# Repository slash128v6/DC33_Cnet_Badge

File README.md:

# DC33 CompuNet Badge - The Meshtastic Express

Introducing **The Meshtastic Express** — the open-source, networkless pager built for hackers, tinkerers, and technophiles. Powered by the Meshtastic protocol and fully customizable from the firmware up, this device lets you send messages over a decentralized mesh network — no cell towers, no Wi-Fi, no problem. Flash your own firmware, tweak the hardware with this highly customizable device and relive the 1990’s glory of belt-clip attached electronics.

Meshtastic devices use **LoRa (Long Range)** radio technology to send small data packets over several kilometers. Each device acts as a node in the mesh, forwarding messages to others until they reach their destination. Learn more at: 

[https://github.com/slash128v6/DC33_Cnet_Badge](https://github.com/slash128v6/DC33_Cnet_Badge)

[https://meshtastic.org](https://github.com/slash128v6/DC33_Cnet_Badge)

> [!TIP]
> **WARNING – DO NOT POWER THE HELTEC V3 LoRa UNIT WITHOUT THE ANTENNA ATTACHED! DAMAGE MAY RESULT**

# Section 1: Hardware Assembly

1.	Verify inventory:

| Qty	| Description |
|------|-------------|
|1	|PCB |
|1	|Heltec V3 LoRa Module Kit (includes antenna and 2x 18 pin headers)|
|1	|LiPo Battery|
|1	|GPS Module|
|1	|GPS Antenna|
|1	|Piezo Buzzer|
|1	|Vibration Motor|
|1	|6 Pin SAO Header|
|1	|12 Pin Header|
|2	|VHB Pads|
|1	|Case Bottom|
|1	|Case Top|
|1	|Case Clip|

2.	Solder the vibration motor. You can trim the wires but be very careful when stripping the ends, as the wire is very small gauge and easy to cut when stripping. Peel off the white tab and stick to the PCB. 

3.	Solder the 6 pin SAO header with the tab aligned with the white silkscreen outline. Try to keep it as square as possible so SAOs are not crooked when installed. 

4.	Solder the piezo buzzer noting the polarity. Remove the protective white sticker.

5.	Solder the Heltec V3 LoRo module to the PCB using the 2x 18 pin headers included in the kit. The short side of the pins should face up through the module and the long side should face down through the PCB. To save time soldering, only the pins marked with white dots need to be soldered. Be careful soldering the 2 pins under the display ribbon cable. The cable is heat resistant, but can melt with too much heat.

6.	Cut off 4 pins from the 12 pin header and solder the GPS module to the PCB. The short side of the pins should face up through the module and the long side should face down through the PCB.

7.	Attach the GPS antenna to the GPS module, pressing the connectors together until there is a slight click and they are parallel when viewed from the side. A fingernail or small flat bladed tool is helpful. Using one of the VHB pads affix the GPS antenna to the PCB, routing the wire underneath the lip. Make sure the GPS antenna is within the white square outline so the case will fit on later.

8.	Mount the PCB in the lower case. Route the LoRa antenna horizontally along the top edge of the PCB as shown. A piece of tape helps. Align the top half of the case onto the lower half posts and press together until the gap between the two halves is gone. 

Slide the clip into the opening on the back until it clicks into place. 

# Section 2: Flashing & Configuration

1.	Install the CP210x Universal Windows Driver from https://www.silabs.com/developer-tools/usb-to-uart-bridge-vcp-drivers?tab=downloads. 

2.	Connect the Heltec Lora V3 module to your PC with a USB-C cable. Open a browser to flasher.meshtastic.org. 

3.	Click “Select Target Device” and select the “Heltec V3” device. 

4.	Select the latest stable firmware from the dropdown menu. 

5.	Click “Flash”. 

6.	Click “Continue”.

7.	Toggle on the options “Full Erase and Install” and “Bundle Web UI” and click “Erase Flash and Install”. 

8.	A selection dialog will appear. Select the CP2102 device and click “Connect”. 

9.	Flashing will begin. Wait for it to complete. 

10. Go to client.meshtastic.org and click “New Connection”. Don’t leave the flasher page open in another tab as it can interfere with the client connection. 

11. Click on the “Serial” tab, then “New Device”. 

12. A selection dialog will appear. Select the CP2102 device and click “Connect”. 

13. Click the new device that appears. 

14. Click on Config in the left menu, then the LoRa tab, set the location to “US”, then click the save floppy icon in the upper right corner. After the setting is saved the Heltec module will reboot. If it does not then try refreshing the page and try again.

15. Reconnect and click on the Display tab, set the Carousel Display to “15”, then click the save floppy icon in the upper right corner. After the setting is saved the Heltec module will reboot. If it does not then try refreshing the page and try again.

16. Reconnect and click on the Position tab, set GPS Mode to Enables, the Receive Pin to “48” and the Transmit Pin to “47” then click the save floppy icon in the upper right corner. After the setting is saved the Heltec module will reboot. If it does not then try refreshing the page and try again.

17. Reconnect and click on Config and Module Config in the left menu, then the Ext Notif tab. Toggle on Enable External Notification then set Output Vibrate to “45” and Output Buzzer to “46” and enable all the toggle items EXCEPT “Use I2S Pin as Buzzer”, then click the save floppy icon in the upper right corner. After the setting is saved the Heltec module will reboot. If it does not then try refreshing the page and try again.

# Section 3: Operation

1.	There are 2 buttons on the left side of the display. Some common button commands:

	*	Brief single presses of the top button will cycle through the screens on the display. By default the screen will turn off after 15 seconds. You can use the top button to wake the display. You can also set a longer screen timeout in settings.
	
	*	A long press of the top button will put the device in shutdown mode.

	*	A triple short press of the top button will disable GPS. Repeat to re-enable GPS.

	*	A single press of the top button will wake it back up. A single press of the bottom button will reboot the device. 

2.	Download the Meshtastic app to your mobile device. It is supported on iOS and Android. Enable Bluetooth on your mobile device then open the Meshtastic app and go to the “Bluetooth” tab. You should see a list of available radios. Tap the radio with the ID that matches your device. You can view it on the info screen by cycling through with the top button.

3.	It will ask for a PIN that will be displayed on your radio’s display. Enter that PIN to connect

4.	The “Messages” tab is where you will send and receive messages. The “Primary Channel” reaches everyone on the mesh. 

5.	At this point you should have basic functionality. Feel free to explore the docs at [https://meshtastic.org/docs/introduction/](https://github.com/slash128v6/DC33_Cnet_Badge). Settings can be managed in the app as well, vs connecting to a PC and using the web interface at [https://client.meshtastic.org/](https://github.com/slash128v6/DC33_Cnet_Badge), though the web interface has more functionality. There is also a Python cli interface that allows bulk configuration changes and backup & restore. This is also covered on the Meshtastic website. A YAML config file with the basic settings applied in this doc is included in the “Software/configs” directory of the repo.

```
# start of Meshtastic configure yaml
config:
  device:
    buzzerGpio: 46
  display:
    autoScreenCarouselSecs: 15
    screenOnSecs: 31536000
  lora:
    region: US
  position:
    gpsMode: ENABLED
    rxGpio: 48
    txGpio: 47
module_config:
  externalNotification:
    active: true
    alertBell: true
    alertBellBuzzer: true
    alertBellVibra: true
    alertMessage: true
    alertMessageBuzzer: true
    alertMessageVibra: true
    enabled: true
    outputBuzzer: 46
    outputVibra: 45
    usePwm: true
```

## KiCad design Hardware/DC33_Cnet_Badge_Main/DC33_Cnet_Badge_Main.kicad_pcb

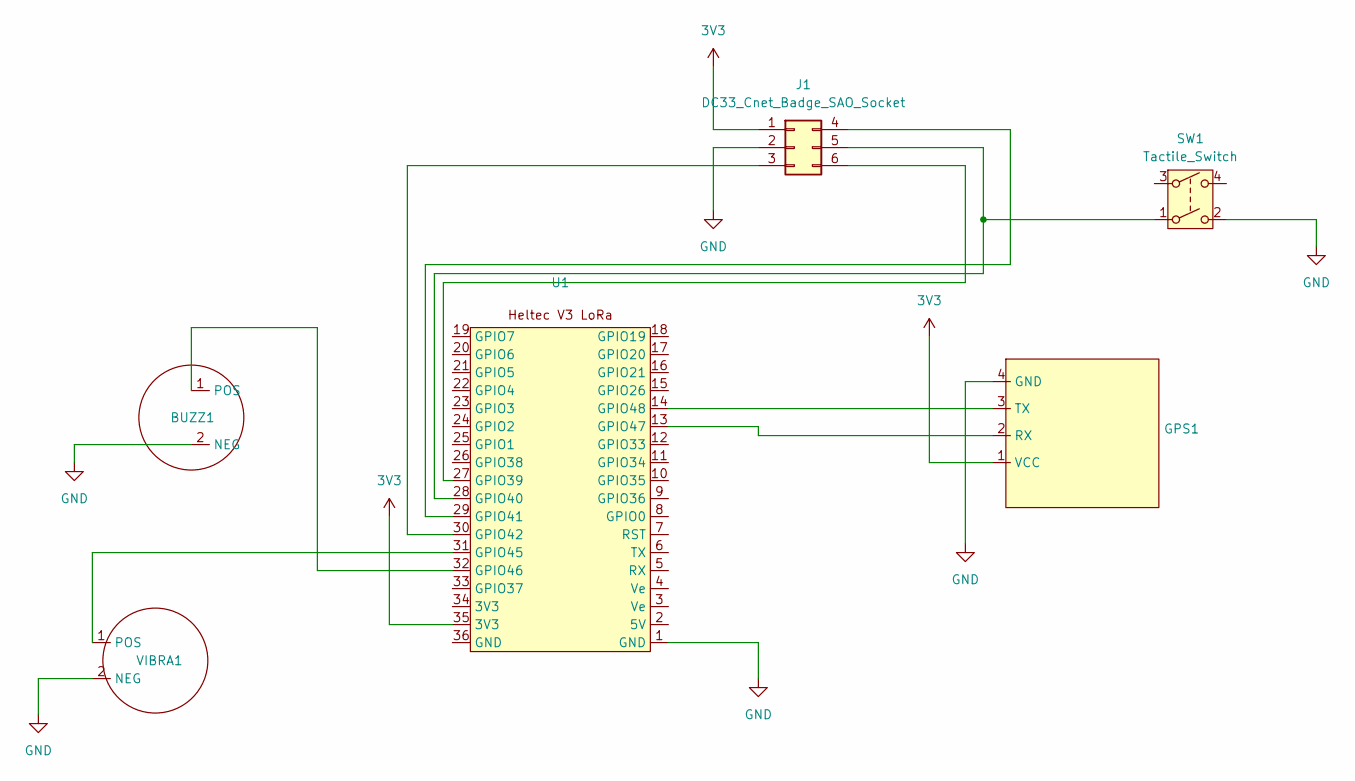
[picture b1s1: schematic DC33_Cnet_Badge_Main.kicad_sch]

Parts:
BUZZ1: DC33_Cnet_Badge_Buzzer
GPS1: DC33_Cnet_Badge_HiLetgo_GPS
J1: DC33_Cnet_Badge_SAO_Socket
SW1: Tactile_Switch; Tactile_Switch-13mm
U1: DC33_Cnet_Badge_Heltec_V3_LoRa
VIBRA1: DC33_Cnet_Badge_Vibra

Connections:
3V3: GPS1.1 (VCC), J1.1 (+3.3V), U1.35 (3V3)
GND: BUZZ1.2 (NEG), GPS1.4 (GND), J1.2 (GND), SW1.2, U1.1 (GND), VIBRA1.2 (NEG)
unnamed: BUZZ1.1 (POS), U1.32 (GPIO46)
unnamed: GPS1.2 (RX), U1.13 (GPIO47)
unnamed: GPS1.3 (TX), U1.14 (GPIO48)
unnamed: J1.5 (GPIO1), SW1.1, U1.28 (GPIO40)
unnamed: J1.6 (GPIO2), U1.27 (GPIO39)
unnamed: J1.4 (SCL), U1.29 (GPIO41)
unnamed: J1.3 (SDA), U1.30 (GPIO42)
unnamed: U1.31 (GPIO45), VIBRA1.1 (POS)

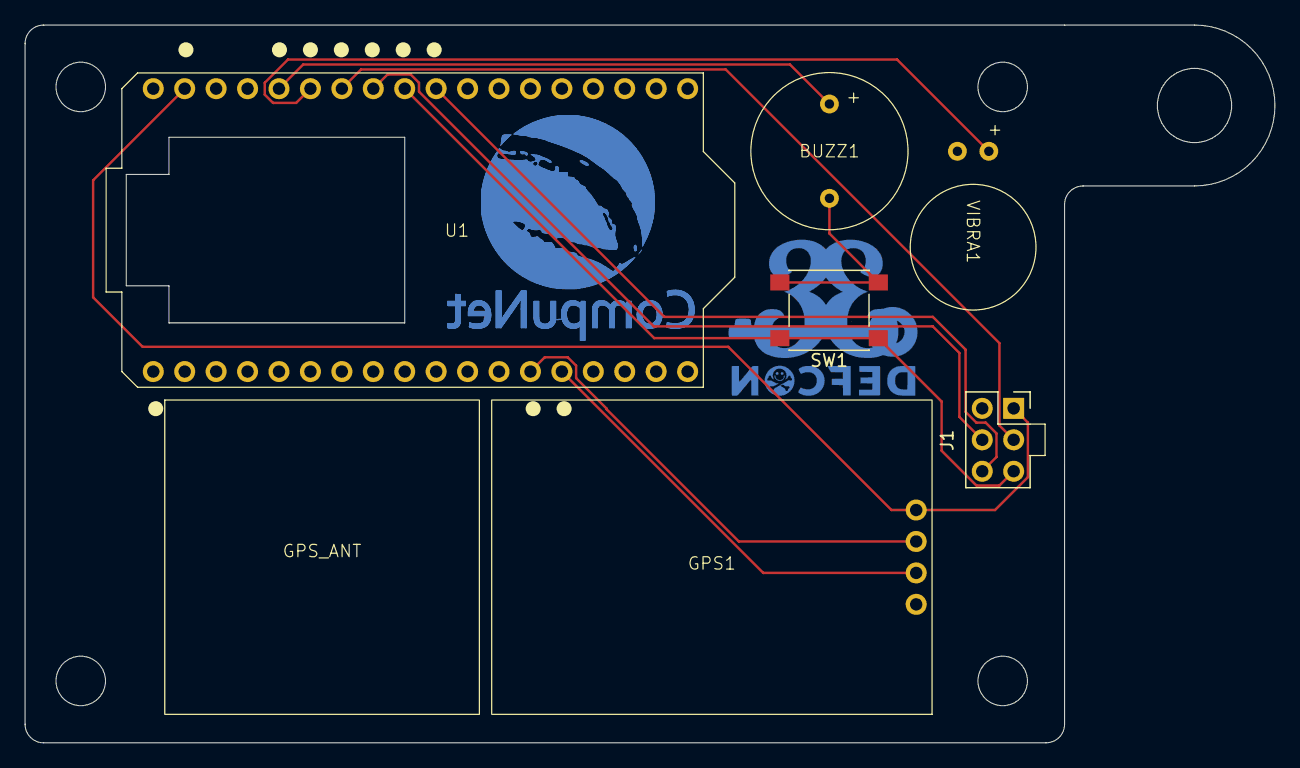
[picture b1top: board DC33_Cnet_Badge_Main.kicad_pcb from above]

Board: 2 copper layers, 101.0 x 58.0 mm, 8 parts (1 on the bottom side), 10 nets.

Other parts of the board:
GPS_ANT: DC33_Cnet_Badge_HiLetgo_GPS_Ant
LiPo: DC33_Cnet_Badge_LiPo

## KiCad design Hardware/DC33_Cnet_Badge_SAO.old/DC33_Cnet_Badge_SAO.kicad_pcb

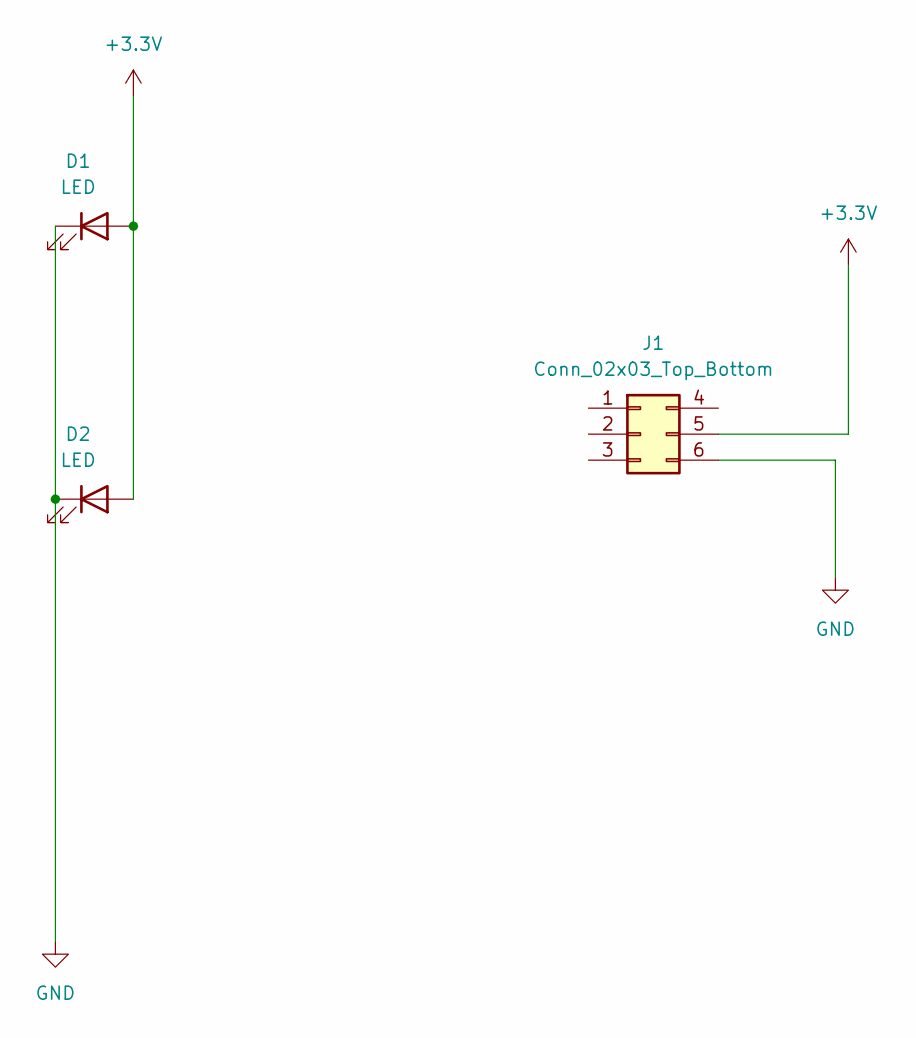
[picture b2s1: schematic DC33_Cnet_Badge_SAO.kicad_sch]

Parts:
D1, D2: LED; LED_D3.0mm
J1: Conn_02x03_Top_Bottom; PinSocket_2x03_P2.54mm_Vertical_Tab

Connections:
+3.3V: D1.2 (A), D2.2 (A), J1.5
GND: D1.1 (K), D2.1 (K), J1.6

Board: 2 copper layers, 3 parts (1 on the bottom side), 2 nets, no tracks yet.

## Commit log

2024-09-09 Remove Private
2024-12-05 Updated prototype PCB
2024-12-05 Removed old files
2024-12-09 Added 3D models
2024-12-09 FreeCAD model
2024-12-09 Incremental commit
2024-12-10 KiCad 3D Models
2024-12-13 Case_1 Files
2024-12-14 Case updates
2024-12-14 Case clip
2024-12-14 Case clip update
2024-12-15 Clip update
2024-12-15 8008135
2024-12-17 Case updates - PETG
2024-12-17 Case clip updates
2024-12-23 Added default ringtone config
2025-01-10 Incremental Updates
2025-03-21 Updated case
2025-03-24 Updated PCB
2025-05-05 SAO Updates
2025-05-23 Latest updates
2025-05-23 Clean up
2025-06-09 Added docs assets
2025-06-10 Update Docs
2025-06-10 Doc updates
2025-06-10 Cleanup
2025-07-22 Updated docs
2025-07-28 Added schematics
2025-08-01 Doc update
2025-08-01 readme updated
